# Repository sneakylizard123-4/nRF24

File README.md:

# nRF24 Breakout Board

A small 2.4GHz module based on the nRF24L01P+, with an SMA jack for an external
antenna, an on-board RFX2401C PA/LNA for extra range, and a breadboard friendly
SPI header. Runs from 3.3V or 5V off an on-board LDO.

## Custom Features

- nRF24L01P+ 2.4GHz transceiver
- RFX2401C external PA/LNA for roughly +20dBm in TX and LNA gain in RX
- Discrete LC balun + harmonic filter
- LC match and DC block from the PA/LNA out to the SMA jack
- Right-angle SMA jack mounted on the board edge, for a real whip or panel antenna
- 16MHz crystal with matched load caps and bias resistor
- PA supply decoupled separately from the digital rail
- TLV75733 LDO: feed the header 3.3V or 5V and the board regulates itself
- 1x08 2.54mm header for drop-in SPI control from any MCU
- 2x M3 mounting holes

## How It Works

- The host MCU talks SPI over the header.
- The nRF24L01P+ differential PA outputs go through the LC balun and harmonic filter to become a single 50 ohm line which lands on the RFX2401C PA/LNA.
- The PA amplifies it and sends it through an LC match and DC block onto the SMA jack. In the other direction the LNA boosts received signals back down the same line.

The 16MHz crystal clocks the radio, a 1M bias resistor plus 22pF load caps set
the oscillator frequency.

### Power Tree

```mermaid
graph LR
  VIN[VIN: header pin 2, 3.3V or 5V]
  VIN --> LDO[U2 TLV75733]
  LDO --> R[+3.3V rail]
  R --> R1[U1 nRF24L01P+]
  R --> R2[U3 RFX2401C PA/LNA]
  R1 -->|ANT1/ANT2| Balun[LC balun + harmonic filter]
  Balun --> R2
  R2 --> Match[LC match + DC block]
  Match --> SMA[J2 antenna port]
```

## PCB Design

50.0 x 30.0 mm, 4-layer, 1.6mm thick, 5mm radius corners, on the JLCPCB
JLC04161H-7628 stackup. F.Cu carries the routing, In1.Cu is a solid ground
plane, In2.Cu is the +3.3V plane, and B.Cu has the leftover CE and VIN runs.

The PA/LNA sits on the RF line between the radio and the SMA, which hangs off the board edge.

## Usage

- The 3.3V rail comes from the on-board TLV75733, so the header VIN pin accepts 3.3V or 5V. The radio itself is a 3.3V part and is not 5V tolerant, which is what the LDO is there for.
- The radio talks SPI to your MCU. Neither the nRF24L01P+ nor the RFX2401C needs firmware of its own; you drive CE, CSN and IRQ from your own code.
- Fit an antenna on J2 before powering up. Do not run the PA into a transmitter with no load.

| Pin | Function        |
|-----|-----------------|
| 1   | GND             |
| 2   | VIN (3.3-5V)    |
| 3   | CE              |
| 4   | CSN             |
| 5   | SCK             |
| 6   | MOSI            |
| 7   | MISO            |
| 8   | IRQ             |

## BOM (Bill of Materials)

| Item | Cost |
|------|------|
| Components (per board) | $6.55 |
| Components (first order, MOQ rounded, 5 boards) | $20.12 |
| PCB (qty 5, 4-layer) | $8.10 ($1.62/board) |
| Controlled impedance (optional) | not quoted |
| **Total (5 boards, parts + boards)** | **$28.22** |
| Shipping (economy direct line, 8-13 business days) | $8.47 |

Quoted 2026-09-29 from the JLCPCB instant quote on the uploaded gerbers. The
detected board is 4 layer 30x50mm, qty 5. The $8.10 is a web-tier price made up of
a $8.00 promo plus $0.10 edge rounding; the JLCONE desktop tier came out at $2.10
for the same order. Shipping, tax, rush and controlled impedance are all outside
that number. Confirm the total at checkout, the promo may not persist.

See [BOM.csv](BOM.csv) for the full part list with LCSC part numbers, prices and
supplier links.

## Production

Not built yet. Board house is JLCPCB, 4-layer FR4 on the JLC04161H-7628
stackup, 1.6mm, HASL (lead-free), green, 50.0 x 30.0 mm inside a 100x100mm
panel, qty 5. That stackup puts 0.2104mm of prepreg between F.Cu and In1.Cu, so
the antenna trace on F.Cu references a ground plane 0.2104mm away, and In2.Cu
carries the +3.3V plane.

The board is hand-routed, no autorouter. The antenna-side net (`U3-ANT`) runs
as single-ended 0.4mm microstrip on F.Cu from the RFX2401C antenna pin to J2,
with the matching network (C19, L4, C20, C21, L5, C22) as an alternating LC
ladder along the way. The nRF24 differential PA outputs (`U1-ANT1`, `U1-ANT2`)
are also 0.4mm and stay paired until the balun. 221 through vias, mostly
stitching the top layer down to the In1.Cu ground plane.

The 0.4mm width is close but not exact. Over 0.2104mm of prepreg, 0.4mm works
out to 54 ohm and 0.46mm works out to 50, which stays inside the 45-55 ohm band
that JLCPCB's published +/-10% impedance tolerance allows on 4 layer and up. The
0.06mm change has not been made yet. See Known Issues.

## Repository Structure

```
|-- kicad/            # PCB source files (.kicad_sch / .kicad_pcb)
|   |-- parts/        # Project-local symbol / footprint / 3D libs
|   `-- production/   # Gerbers, drill files, netlist, position files
|-- images/           # Schematic exports and renders
|   |-- schematic/    # Per-sheet PNGs
|   |-- pcb/          # Layout progress shots
|   `-- screenshots/  # Build photos
|-- BOM.csv           # Bill of materials w/ links + total cost line
|-- JOURNAL.md        # Work journal
|-- LICENSE           # CERN OHL v2-P (hardware)
`-- LICENSE-MIT       # MIT (code)
```

## Known Issues

- Board is routed but unassembled and untested
- The antenna-side trace is 0.4mm over 0.2104mm of prepreg, which works out to 54 ohm rather than 50. 0.46mm is the correct width: 50 ohm nominal, inside the 45-55 ohm band JLCPCB publishes as its +/-10% tolerance on 4 layer. It is a 0.06mm change to 16.8mm of track and has not been made yet
- The F.Cu ground pour still runs right up to the antenna trace. On 4 layers that turns the trace into a coplanar waveguide and drops it below the calculated figure, so In1.Cu is not yet the only reference. The pour has to be cleared back from that run before the width number above means anything
- Two segments on the antenna nets are still 0.2mm rather than the surrounding width. 0.2mm is about 110 ohm on this stackup, so that is fine as pad fanout and a step discontinuity anywhere else. Worth checking which of the two it is
- All 221 vias are through vias, so every ground via punches an anti-pad in the In2.Cu +3.3V plane. Harmless at 3.3V, but it is a lot of voids in the rail
- The board render in PCB Design predates the move to 4 layers
- PA/LNA match uses tight-tolerance parts (0.3pF / 1.5pF / 2.4nH); the values may need tuning on the first real board
- TXEN/RXEN control of the RFX2401C is wired to VDD_PA and CE through 1k resistors - direction switching is a prototype hack, revisit if it misbehaves
- Two schematic parts are not orderable as drawn, so the footprints need editing before fabrication
  - L1 (2.3nH) and L3 (7.9nH) are drawn as 0603 but no 0603 part exists at those values; every 0603-numbered 2.3nH in the catalog is physically 0201. Both are specced as 0402, which lands inside the existing 0603 pads so no traces have to move
  - X1 was drawn as HC-52/U, which no supplier carries. The footprint is now an SMD 3225 4-pad and the BOM specced an SMD 3225 part to match, so this one is resolved. Worth knowing: the load caps are 22pF, which puts the network at roughly 13-15pF against a 12pF crystal, so it will run slightly low. The 22pF is the odd one out, not the crystal
- L2 (12nH) has a self-resonant frequency of 3GHz, uncomfortably close to the 2.4GHz operating point. 0603 inductors are marginal this high up; if the match does not settle, the fix is a larger inductor package, not a different value
- J2 is a generic 4-post THT SMA standing in for the Amphenol 901-143 the footprint is named after. The datasheet drawing for the substitute has not been checked against the footprint's ground-post pattern, so confirm the two agree before ordering boards
- U1 is a genuine Nordic nRF24L01P. The Si24R1 is pin-compatible and about 5x cheaper, but it is a different part and the radio registers and PA current draw both shift, so it sits in the BOM notes rather than in the design
- The U2 footprint value says TLV75733PDBV while the orderable part is the PDBVR tape-and-reel variant. Same die, different suffix, but the BOM carries the orderable one

## Credits & Inspiration

- [nRF24L01+ Product Spec](https://www.nordicsemi.com/products/nrf24l01) - reference balun/matching values and pinout
- RFX2401C symbol and footprint from the incutec-KiCad-Library (OpenRX FPGA project)

## License

Hardware (schematics, PCB layout, CAD and 3D models) is under
[CERN OHL v2-P](LICENSE), the permissive variant, because this is a personal
build and not a product. If boards are ever sold, relicense to CERN-OHL-S.

    SPDX-License-Identifier: CERN-OHL-P-2.0

Any code in this repository (build scripts, and any firmware added later) is
licensed under the MIT License.

    SPDX-License-Identifier: MIT

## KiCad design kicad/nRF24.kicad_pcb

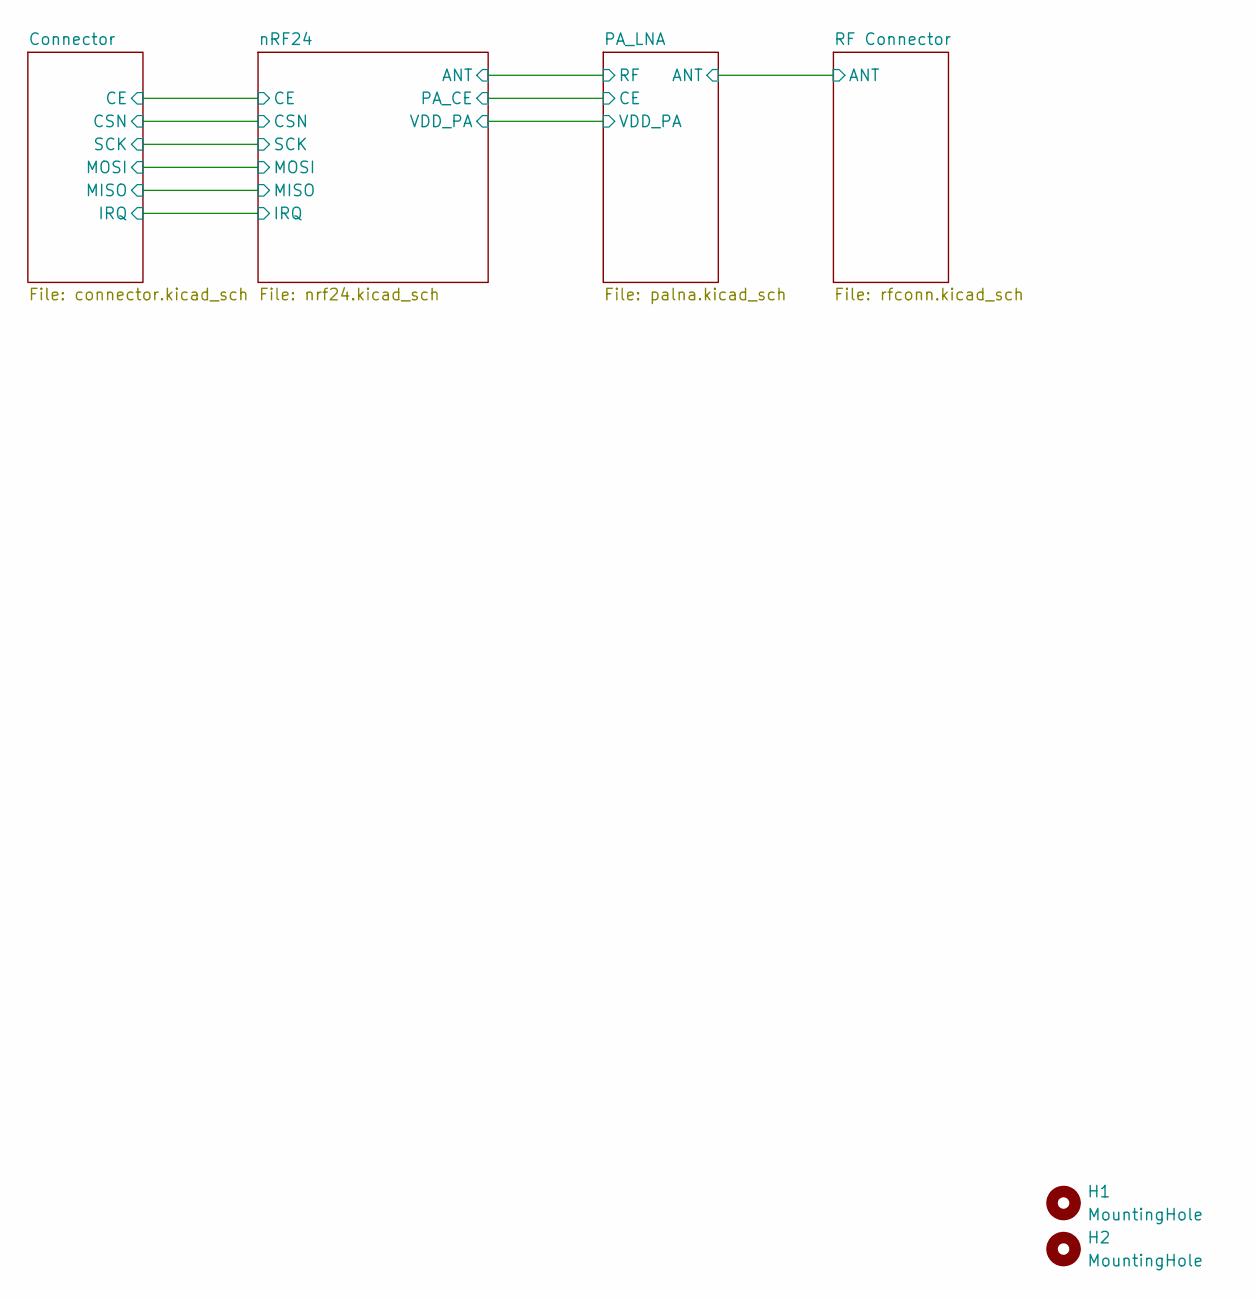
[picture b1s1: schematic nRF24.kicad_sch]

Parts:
H1, H2: MountingHole; MountingHole_3.2mm_M3

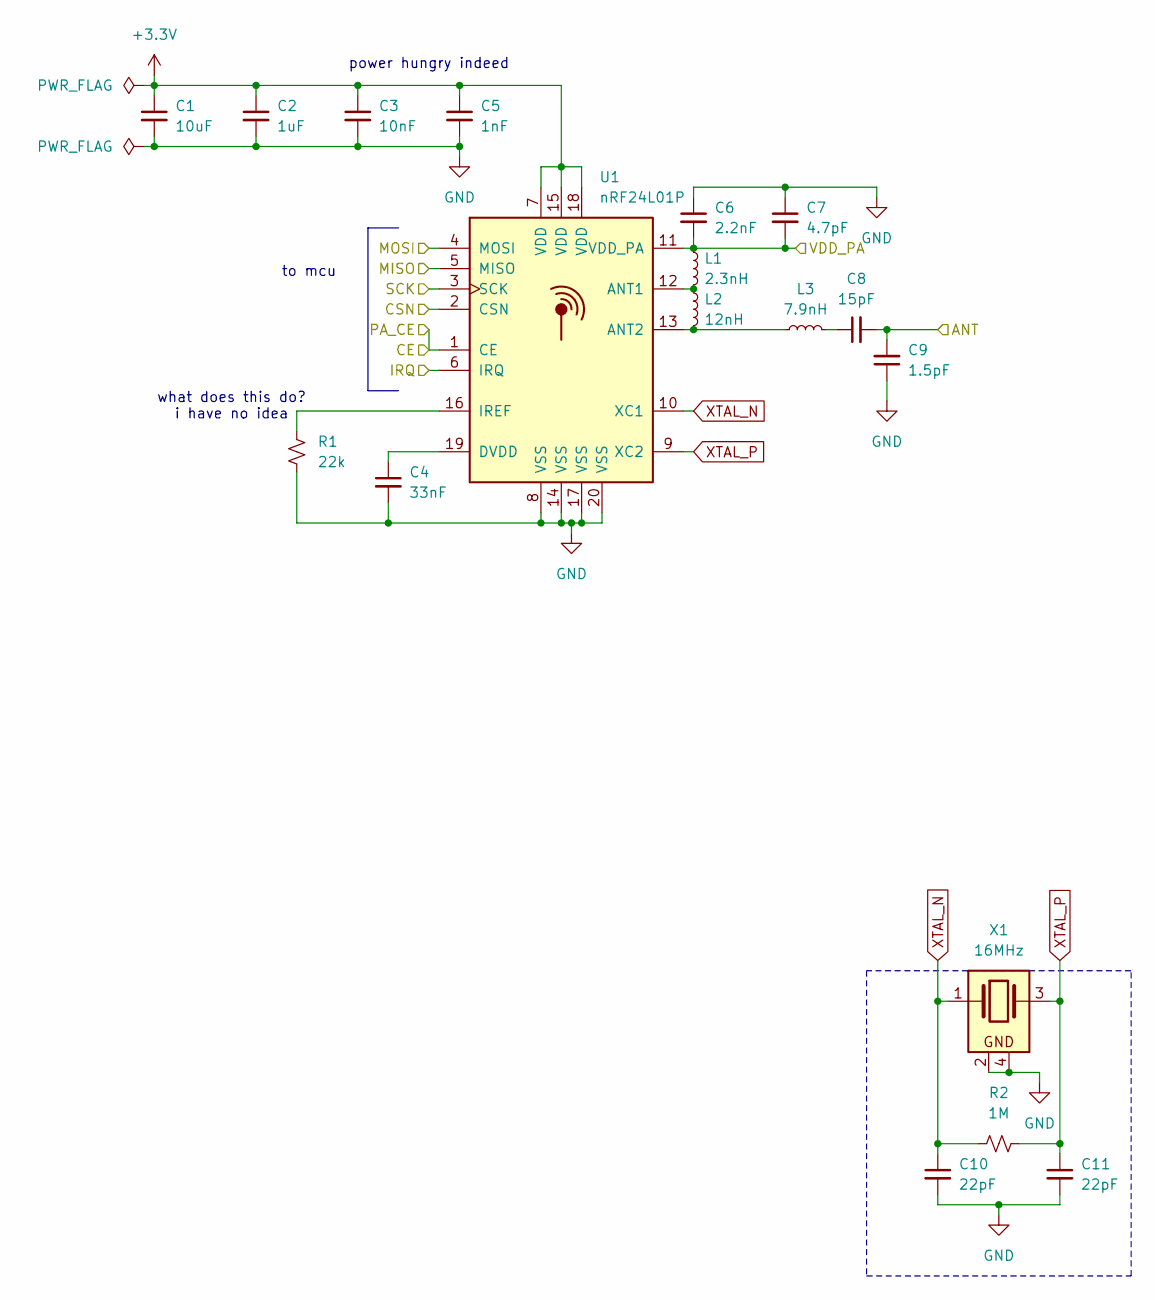
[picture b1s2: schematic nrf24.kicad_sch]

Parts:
C1: 10uF; C_0603_1608Metric
C2: 1uF; C_0603_1608Metric
C3: 10nF; C_0603_1608Metric
C4: 33nF; C_0603_1608Metric
C5: 1nF; C_0603_1608Metric
C6: 2.2nF; C_0603_1608Metric
C7: 4.7pF; C_0603_1608Metric
C8: 15pF; C_0603_1608Metric
C9: 1.5pF; C_0603_1608Metric
C10, C11: 22pF; C_0603_1608Metric
L1: 2.3nH; L_0402_1005Metric
L2: 12nH; L_0603_1608Metric
L3: 7.9nH; L_0402_1005Metric
R1: 22k; R_0603_1608Metric
R2: 1M; R_0603_1608Metric
U1: nRF24L01P; QFN-20-1EP_4x4mm_P0.5mm_EP2.5x2.5mm
X1: 16MHz; Crystal_SMD_3225-4Pin_3.2x2.5mm

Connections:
+3.3V: C1.1, C2.1, C3.1, C5.1, U1.7 (VDD), U1.15 (VDD), U1.18 (VDD); also elsewhere on the board
/Connector/CE: U1.1 (CE); also elsewhere on the board
/Connector/CSN: U1.2 (CSN); also elsewhere on the board
/Connector/IRQ: U1.6 (IRQ); also elsewhere on the board
/Connector/MISO: U1.5 (MISO); also elsewhere on the board
/Connector/MOSI: U1.4 (MOSI); also elsewhere on the board
/Connector/SCK: U1.3 (SCK); also elsewhere on the board
/PA_LNA/RF: C8.2, C9.2; also elsewhere on the board
/PA_LNA/VDD_PA: C6.2, C7.2, L1.1, U1.11 (VDD_PA); also elsewhere on the board
GND: C1.2, C2.2, C3.2, C4.2, C5.2, C6.1, C7.1, C9.1, C10.2, C11.2, R1.2, U1.8 (VSS), U1.14 (VSS), U1.17 (VSS), U1.20 (VSS), X1.2, X1.4; also elsewhere on the board
unnamed: C8.1, L3.2
unnamed: L1.2, L2.1, U1.12 (ANT1)
unnamed: L2.2, L3.1, U1.13 (ANT2)
unnamed: C4.1, U1.19 (DVDD)
unnamed: R1.1, U1.16 (IREF)
XTAL_N: C10.1, R2.1, U1.10 (XC1), X1.1
XTAL_P: C11.1, R2.2, U1.9 (XC2), X1.3

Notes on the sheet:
power hungry indeed
to mcu
what does this do? i have no idea

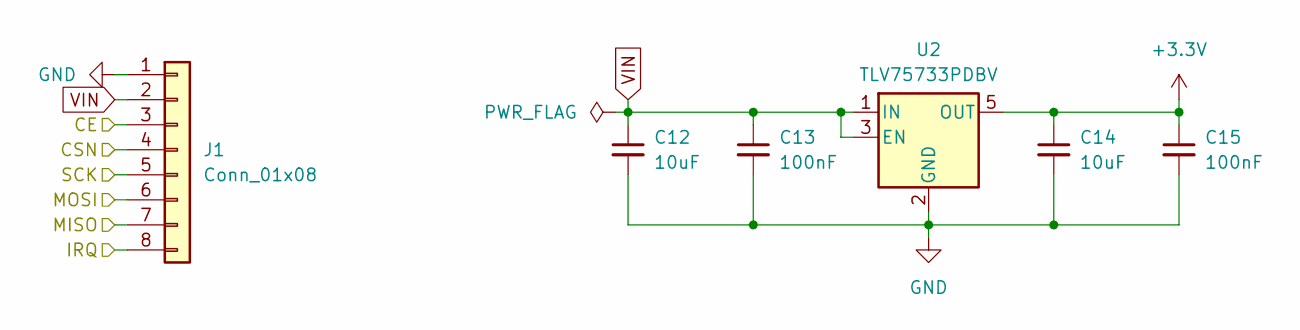
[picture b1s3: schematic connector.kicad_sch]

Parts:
C12, C14: 10uF; C_0603_1608Metric
C13, C15: 100nF; C_0603_1608Metric
J1: Conn_01x08; PinHeader_1x08_P2.54mm_Vertical
U2: TLV75733PDBV; SOT-23-5

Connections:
+3.3V: C14.1, C15.1, U2.5 (OUT); also elsewhere on the board
/Connector/CE: J1.3; also elsewhere on the board
/Connector/CSN: J1.4; also elsewhere on the board
/Connector/IRQ: J1.8; also elsewhere on the board
/Connector/MISO: J1.7; also elsewhere on the board
/Connector/MOSI: J1.6; also elsewhere on the board
/Connector/SCK: J1.5; also elsewhere on the board
GND: C12.2, C13.2, C14.2, C15.2, J1.1, U2.2 (GND); also elsewhere on the board
VIN: C12.1, C13.1, J1.2, U2.1 (IN), U2.3 (EN)

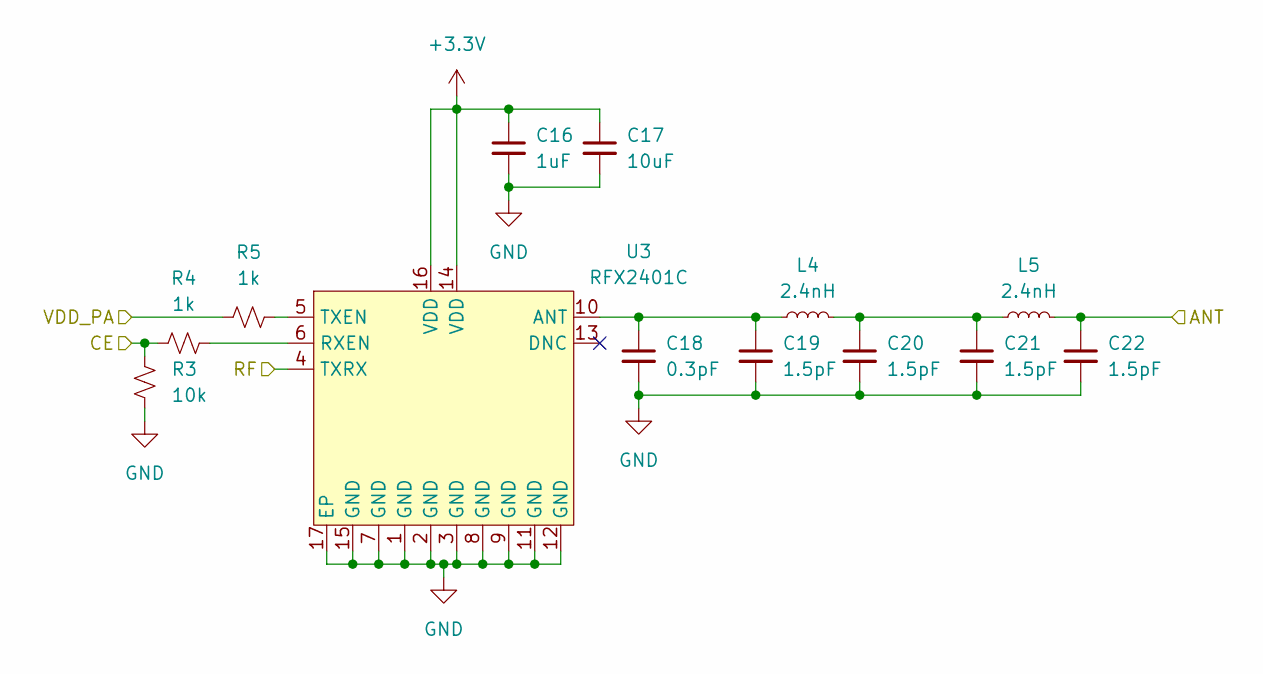
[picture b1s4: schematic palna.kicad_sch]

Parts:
C16: 1uF; C_0603_1608Metric
C17: 10uF; C_0603_1608Metric
C18: 0.3pF; C_0603_1608Metric
C19, C20, C21, C22: 1.5pF; C_0603_1608Metric
L4, L5: 2.4nH; L_0603_1608Metric
R3: 10k; R_0603_1608Metric
R4, R5: 1k; R_0603_1608Metric
U3: RFX2401C; QFN-16_L3.0-W3.0-P0.50-BL-EP1.7; LCSC C19213

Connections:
+3.3V: C16.1, C17.1, U3.14 (VDD), U3.16 (VDD); also elsewhere on the board
/Connector/CE: R3.2, R4.1; also elsewhere on the board
/PA_LNA/ANT: C22.1, L5.2; also elsewhere on the board
/PA_LNA/RF: U3.4 (TXRX); also elsewhere on the board
/PA_LNA/VDD_PA: R5.1; also elsewhere on the board
GND: C16.2, C17.2, C18.2, C19.2, C20.2, C21.2, C22.2, R3.1, U3.1 (GND), U3.2 (GND), U3.3 (GND), U3.7 (GND), U3.8 (GND), U3.9 (GND), U3.11 (GND), U3.12 (GND), U3.15 (GND), U3.17 (EP); also elsewhere on the board
unnamed: C20.1, C21.1, L4.2, L5.1
unnamed: C18.1, C19.1, L4.1, U3.10 (ANT)
unnamed: R4.2, U3.6 (RXEN)
unnamed: R5.2, U3.5 (TXEN)

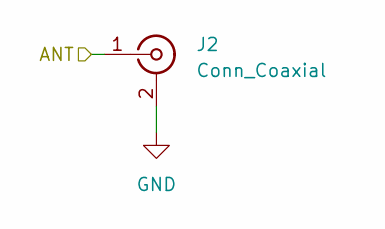
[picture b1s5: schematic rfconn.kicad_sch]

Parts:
J2: Conn_Coaxial; SMA_Amphenol_901-143_Horizontal

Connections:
/PA_LNA/ANT: J2.1 (In); also elsewhere on the board
GND: J2.2 (Ext); also elsewhere on the board

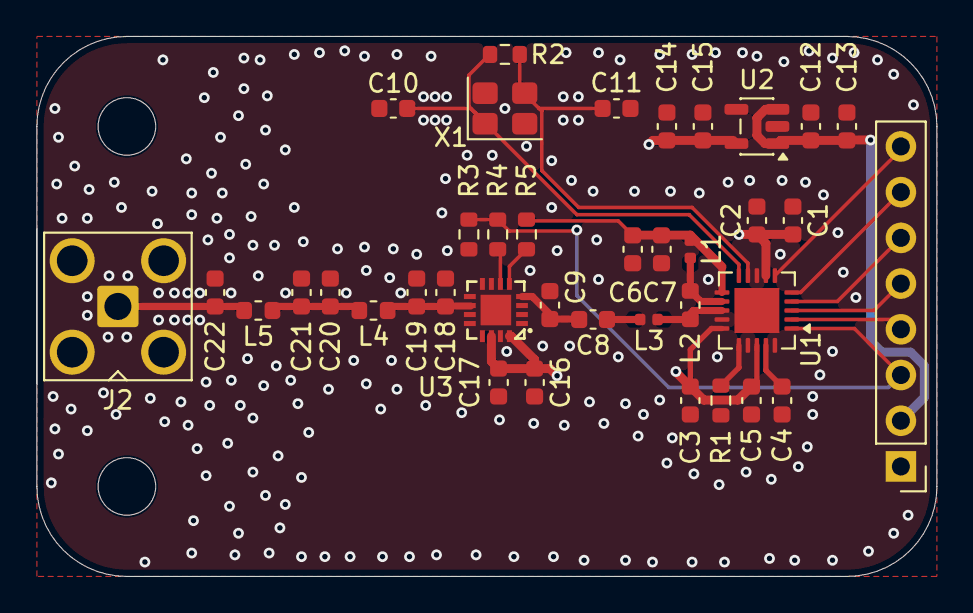
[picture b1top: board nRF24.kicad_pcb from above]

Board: 4 copper layers, 50.0 x 30.0 mm, 40 parts (0 on the bottom side), 23 nets.

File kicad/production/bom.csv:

Designator,Footprint,Quantity,Value,LCSC Part #
"C1, C12, C14, C17",0603,4,10uF,
"C10, C11",0603,2,22pF,
"C13, C15",0603,2,100nF,
"C16, C2",0603,2,1uF,
C18,0603,1,0.3pF,
"C19, C20, C21, C22, C9",0603,5,1.5pF,
C3,0603,1,10nF,
C4,0603,1,33nF,
C5,0603,1,1nF,
C6,0603,1,2.2nF,
C7,0603,1,4.7pF,
C8,0603,1,15pF,
J1,PinHeader_1x08_P2.54mm_Vertical,1,Conn_01x08,
J2,SMA_Amphenol_901-143_Horizontal,1,Conn_Coaxial,
L1,0603,1,2.3nH,
L2,0603,1,12nH,
L3,0603,1,7.9nH,
"L4, L5",0603,2,2.4nH,
R1,0603,1,22k,
R2,0603,1,1M,
R3,0603,1,10k,
"R4, R5",0603,2,1k,
U1,QFN-20-1EP_4x4mm_P0.5mm_EP2.5x2.5mm,1,nRF24L01P,
U2,SOT-23-5,1,TLV75733PDBV,
U3,QFN-16_L3.0-W3.0-P0.50-BL-EP1.7,1,RFX2401C,C19213
X1,Crystal_SMD_3225-4Pin_3.2x2.5mm,1,16MHz,
